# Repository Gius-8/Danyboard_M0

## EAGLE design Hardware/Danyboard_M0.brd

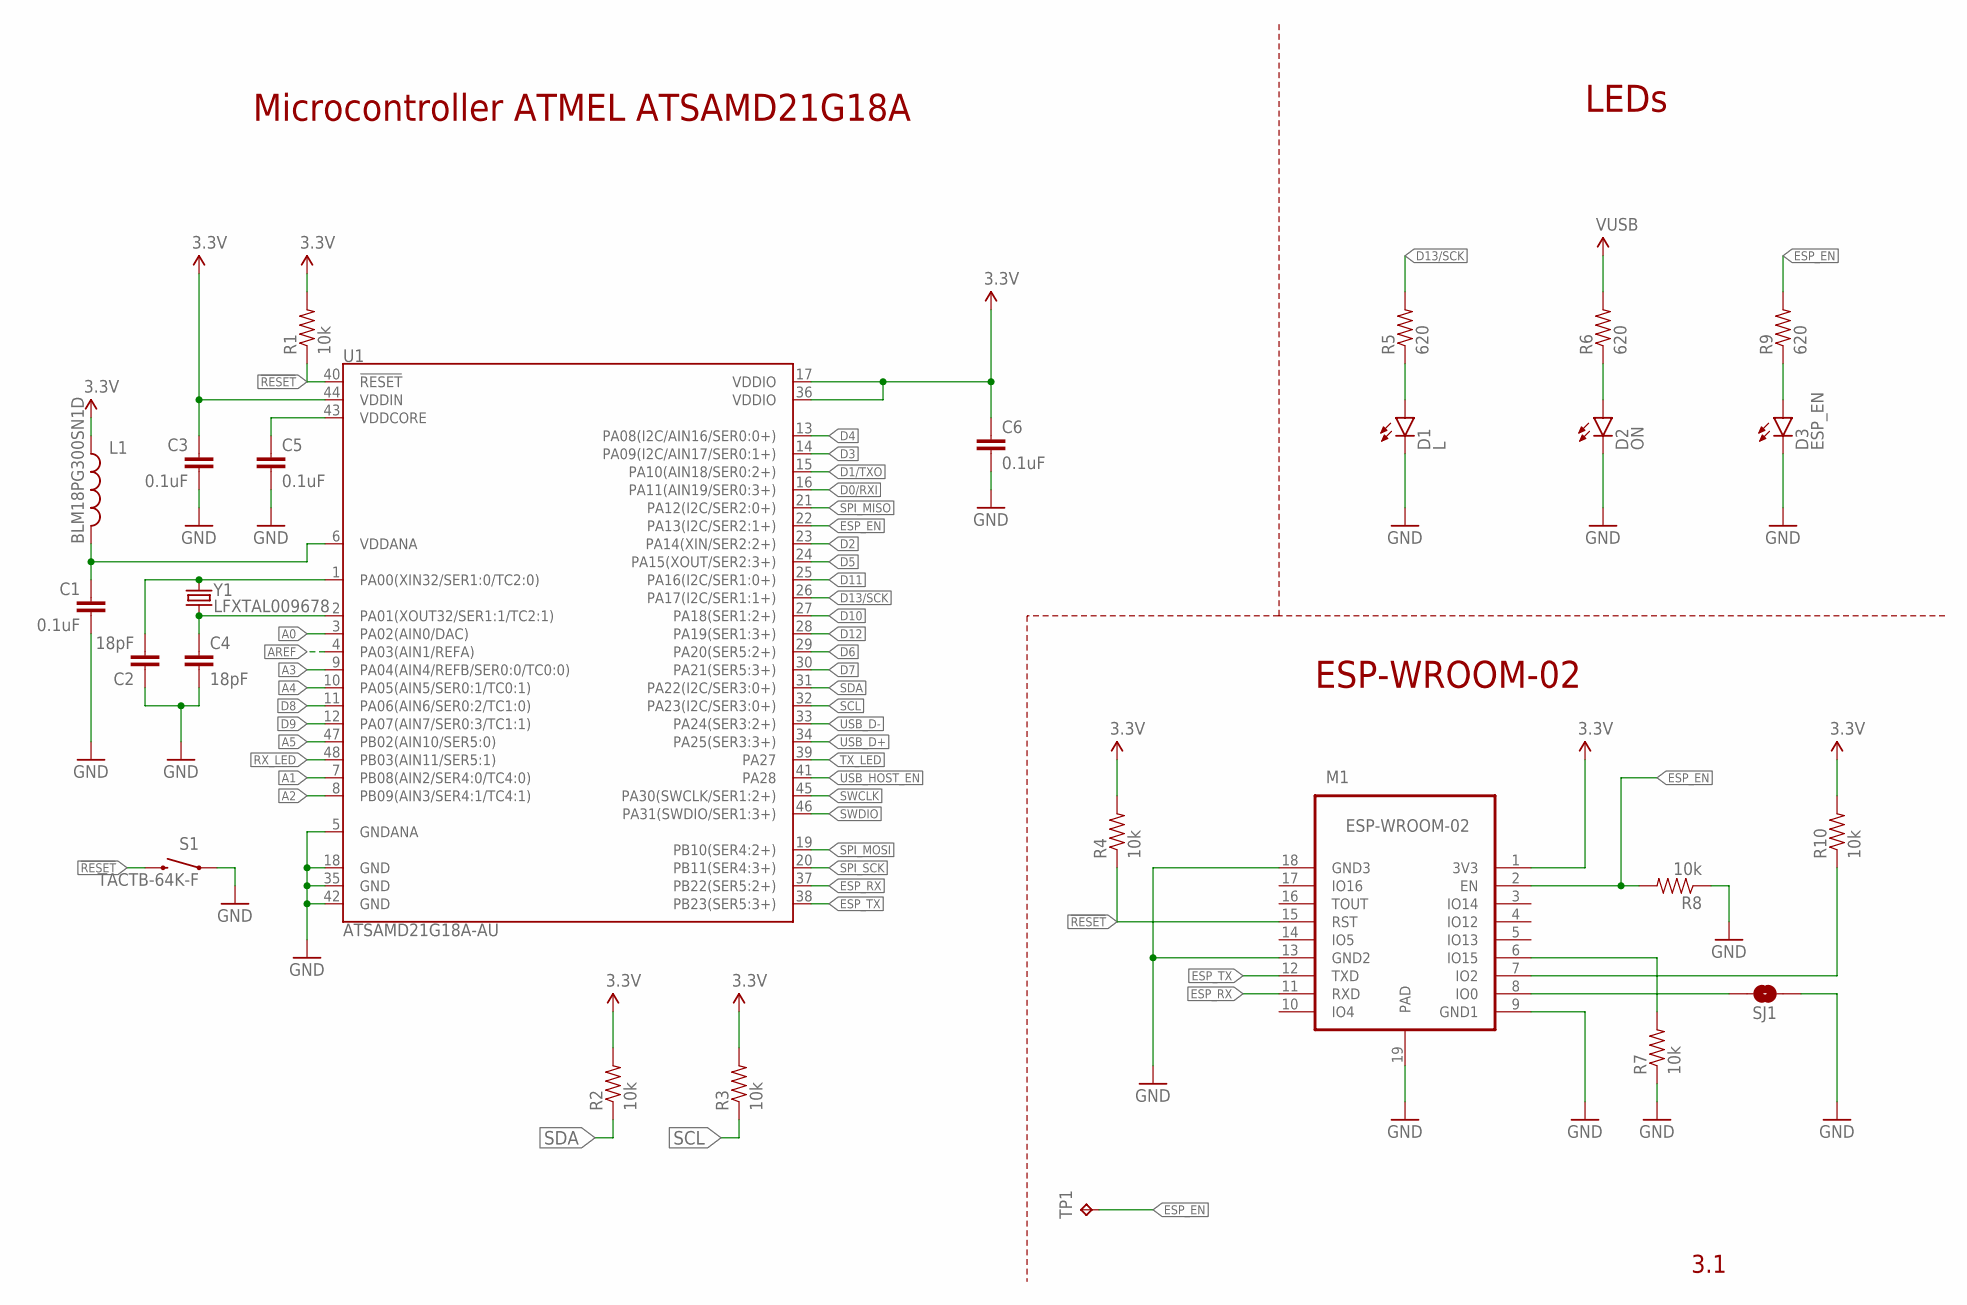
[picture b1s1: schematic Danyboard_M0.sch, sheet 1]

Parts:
C1, C3, C5, C6: 0.1uF; 0603-CAP_NOSILK
C2, C4: 18pF; 0603-CAP_NOSILK
D1: L; LED-0603
D2: ON; LED-0603
D3: ESP_EN; LED-0603
L1: BLM18PG300SN1D; 0603_NOSILK
M1: ESP-WROOM-02; ESP-WROOM-02_NOSILK
R1, R2, R3, R4, R7, R8, R10: 10k; 0603-RES_NOSILK
R5, R6, R9: 620; 0603-RES_NOSILK
S1: TACTB-64K-F; TACTILE-SWITCH-SMD_NOSILK
SJ1: SOLDERJUMPERNO; SJ_2S-NO
TP1: ESP8266; B1,27
U1: ATSAMD21G18A-AU; TQFP-48_NOSILK
Y1: LFXTAL009678; CRYSTAL-SMD-3.2X1.5MM_NOSILK

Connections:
3.3V: C3.1, C6.1, L1.1, M1.1 (3V3), R1.2, R2.2, R3.2, R4.2, R10.2, U1.17 (VDDIO), U1.36 (VDDIO), U1.44 (VDDIN); also elsewhere on the board
!RESET: M1.15 (RST), R1.1, R4.1, S1.3 (2), U1.40 (!RESET!); also elsewhere on the board
A0: U1.3 (PA02(AIN0/DAC)); also elsewhere on the board
A1: U1.7 (PB08(AIN2/SER4:0/TC4:0)); also elsewhere on the board
A2: U1.8 (PB09(AIN3/SER4:1/TC4:1)); also elsewhere on the board
A3: U1.9 (PA04(AIN4/REFB/SER0:0/TC0:0)); also elsewhere on the board
A4: U1.10 (PA05(AIN5/SER0:1/TC0:1)); also elsewhere on the board
A5: U1.47 (PB02(AIN10/SER5:0)); also elsewhere on the board
AREF: U1.4 (PA03(AIN1/REFA)); also elsewhere on the board
D0/RXI: U1.16 (PA11(AIN19/SER0:3+)); also elsewhere on the board
D1/TXO: U1.15 (PA10(AIN18/SER0:2+)); also elsewhere on the board
D2: U1.23 (PA14(XIN/SER2:2+)); also elsewhere on the board
D3: U1.14 (PA09(I2C/AIN17/SER0:1+)); also elsewhere on the board
D4: U1.13 (PA08(I2C/AIN16/SER0:0+)); also elsewhere on the board
D5: U1.24 (PA15(XOUT/SER2:3+)); also elsewhere on the board
D6: U1.29 (PA20(SER5:2+)); also elsewhere on the board
D7: U1.30 (PA21(SER5:3+)); also elsewhere on the board
D8: U1.11 (PA06(AIN6/SER0:2/TC1:0)); also elsewhere on the board
D9: U1.12 (PA07(AIN7/SER0:3/TC1:1)); also elsewhere on the board
D10: U1.27 (PA18(SER1:2+)); also elsewhere on the board
D11: U1.25 (PA16(I2C/SER1:0+)); also elsewhere on the board
D12: U1.28 (PA19(SER1:3+)); also elsewhere on the board
D13/SCK: R5.2, U1.26 (PA17(I2C/SER1:1+)); also elsewhere on the board
ESP_EN: M1.2 (EN), R8.2, R9.2, TP1.TP, U1.22 (PA13(I2C/SER2:1+))
ESP_RX: M1.11 (RXD), U1.37 (PB22(SER5:2+))
ESP_TX: M1.12 (TXD), U1.38 (PB23(SER5:3+))
GND: C1.2, C2.1, C3.2, C4.2, C5.2, C6.2, D1.C, D2.C, D3.C, M1.9 (GND1), M1.13 (GND2), M1.18 (GND3), M1.19 (PAD), R7.1, R8.1, S1.1, SJ1.2, U1.5 (GNDANA), U1.18 (GND), U1.35 (GND), U1.42 (GND); also elsewhere on the board
unnamed: C2.2, U1.1 (PA00(XIN32/SER1:0/TC2:0)), Y1.P$2 (2)
unnamed: C4.1, U1.2 (PA01(XOUT32/SER1:1/TC2:1)), Y1.P$1 (1)
unnamed: D1.A, R5.1
unnamed: M1.6 (IO15), R7.2
unnamed: M1.7 (IO2), R10.1
unnamed: M1.8 (IO0), SJ1.1
unnamed: D3.A, R9.1
unnamed: D2.A, R6.1
RX_LED: U1.48 (PB03(AIN11/SER5:1))
SCL: R3.1, U1.32 (PA23(I2C/SER3:0+)); also elsewhere on the board
SDA: R2.1, U1.31 (PA22(I2C/SER3:0+)); also elsewhere on the board
SPI_MISO: U1.21 (PA12(I2C/SER2:0+)); also elsewhere on the board
SPI_MOSI: U1.19 (PB10(SER4:2+)); also elsewhere on the board
SPI_SCK: U1.20 (PB11(SER4:3+)); also elsewhere on the board
SWCLK: U1.45 (PA30(SWCLK/SER1:2+)); also elsewhere on the board
SWDIO: U1.46 (PA31(SWDIO/SER1:3+)); also elsewhere on the board
TX_LED: U1.39 (PA27)
USB_D+: U1.34 (PA25(SER3:3+)); also elsewhere on the board
USB_D-: U1.33 (PA24(SER3:2+)); also elsewhere on the board
USB_HOST_EN: U1.41 (PA28)
VDDANA: C1.1, L1.2, U1.6 (VDDANA)
VDDCORE: C5.1, U1.43 (VDDCORE)
VUSB: R6.2; also elsewhere on the board

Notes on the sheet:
Microcontroller ATMEL ATSAMD21G18A
LEDs
ESP-WROOM-02
3.1

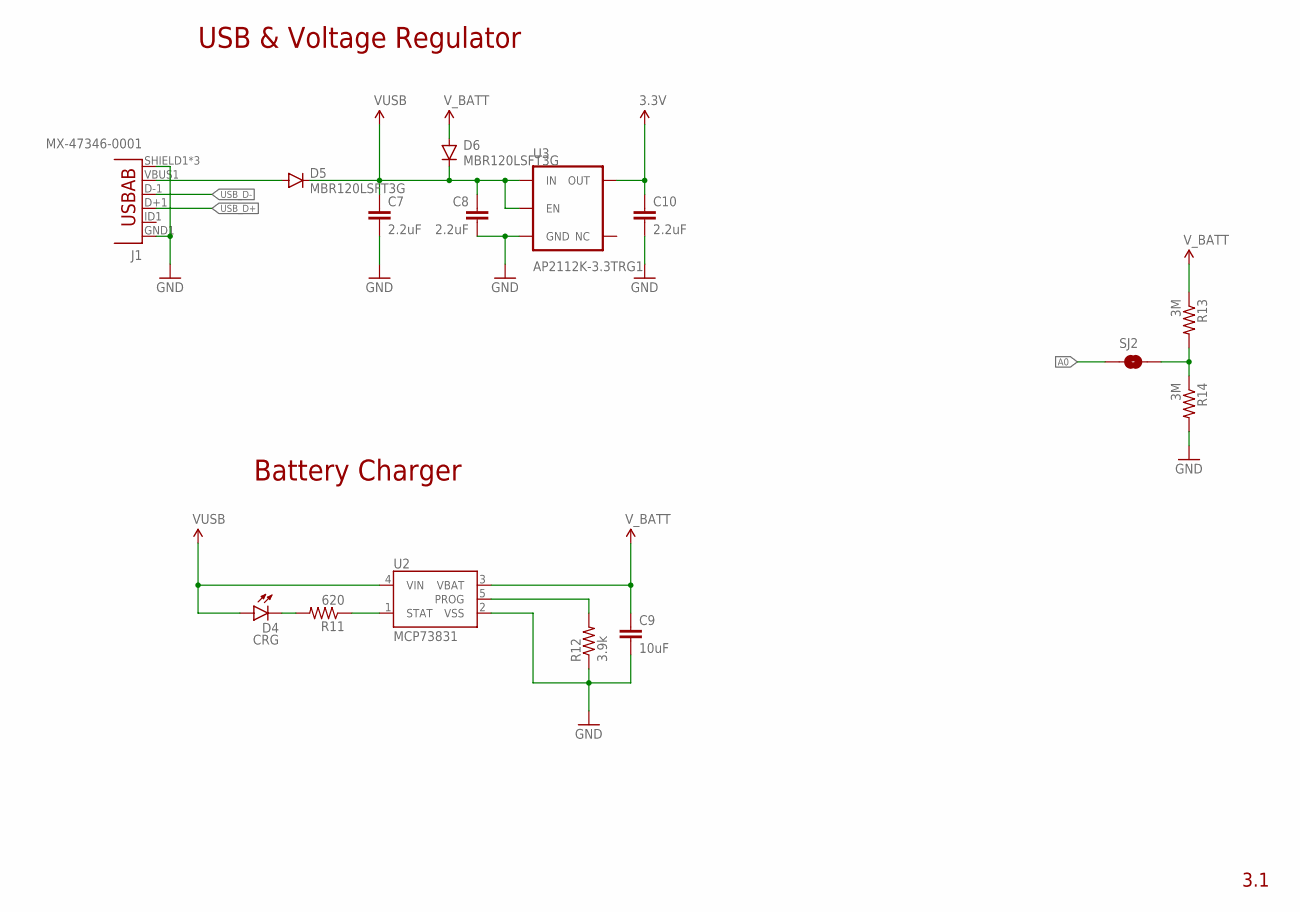
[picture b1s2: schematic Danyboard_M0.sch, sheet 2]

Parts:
C7, C8, C10: 2.2uF; 0603-CAP_NOSILK
C9: 10uF; 0603-CAP_NOSILK
D4: CRG; LED-0603
D5, D6: MBR120LSFT3G; SOD-123_NOSILK
J1: MX-47346-0001; USB-AB-MICRO-SMD_V03
R11: 620; 0603-RES_NOSILK
R12: 3.9k; 0603-RES_NOSILK
R13, R14: 3M; 0603-RES_NOSILK
SJ2: SOLDERJUMPERNO; SJ_2S-NO
U2: MCP73831; SOT23-5
U3: AP2112K-3.3TRG1; SOT23-5

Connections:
3.3V: C10.1, U3.5 (OUT); also elsewhere on the board
A0: SJ2.1; also elsewhere on the board
GND: C7.2, C8.2, C9.2, C10.2, J1.GND1 (GND), J1.SHIELD1 (SHIELD), J1.SHIELD2 (SHIELD), J1.SHIELD3 (SHIELD), R12.1, R14.2, U2.2 (VSS), U3.2 (GND); also elsewhere on the board
unnamed: D4.C, R11.2
unnamed: R11.1, U2.1 (STAT)
unnamed: R12.2, U2.5 (PROG)
unnamed: R13.2, R14.1, SJ2.2
unnamed: D5.A, J1.VBUS1 (VBUS)
USB_D+: J1.D+1 (D+); also elsewhere on the board
USB_D-: J1.D-1 (D-); also elsewhere on the board
VUSB: C7.1, C8.1, D4.A, D5.C, D6.C, U2.4 (VIN), U3.1 (IN), U3.3 (EN); also elsewhere on the board
V_BATT: C9.1, D6.A, R13.1, U2.3 (VBAT); also elsewhere on the board

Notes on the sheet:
USB & Voltage Regulator
Battery Charger
3.1

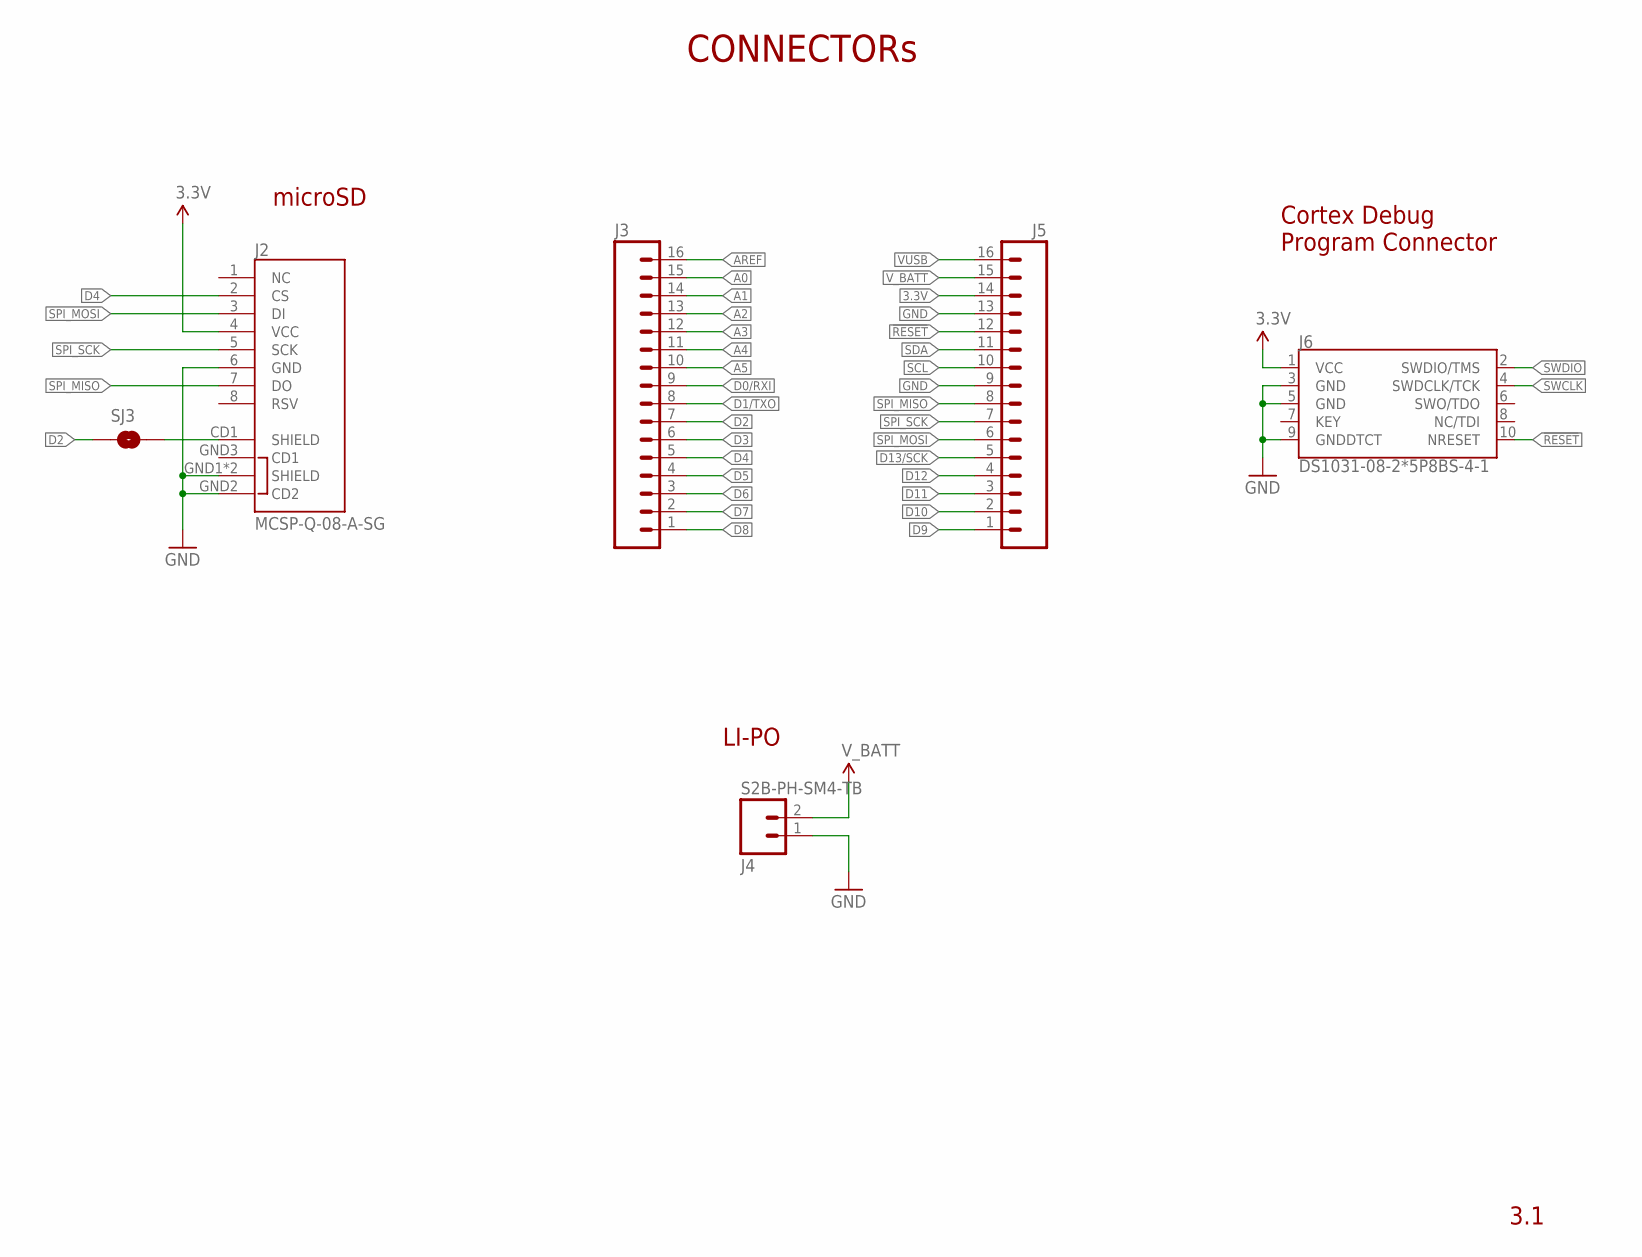
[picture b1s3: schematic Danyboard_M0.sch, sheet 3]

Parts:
J2: MCSP-Q-08-A-SG; MCSP-Q-08-A-SG-T_NOSILK
J3, J5: M161X16_NO_SILK; 1X16_NO_SILK
J4: S2B-PH-SM4-TB; JST-2-SMD_NOSILK
J6: DS1031-08-2*5P8BS-4-1; SAMTECH_FTSH-105-01_NOSILK
SJ3: SOLDERJUMPERNO; SJ_2S-NO

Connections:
3.3V: J2.4 (VCC), J5.14, J6.1 (VCC); also elsewhere on the board
!RESET: J5.12, J6.10 (NRESET); also elsewhere on the board
A0: J3.15; also elsewhere on the board
A1: J3.14; also elsewhere on the board
A2: J3.13; also elsewhere on the board
A3: J3.12; also elsewhere on the board
A4: J3.11; also elsewhere on the board
A5: J3.10; also elsewhere on the board
AREF: J3.16; also elsewhere on the board
D0/RXI: J3.9; also elsewhere on the board
D1/TXO: J3.8; also elsewhere on the board
D2: J3.7, SJ3.1; also elsewhere on the board
D3: J3.6; also elsewhere on the board
D4: J2.2 (CS), J3.5; also elsewhere on the board
D5: J3.4; also elsewhere on the board
D6: J3.3; also elsewhere on the board
D7: J3.2; also elsewhere on the board
D8: J3.1; also elsewhere on the board
D9: J5.1; also elsewhere on the board
D10: J5.2; also elsewhere on the board
D11: J5.3; also elsewhere on the board
D12: J5.4; also elsewhere on the board
D13/SCK: J5.5; also elsewhere on the board
GND: J2.6 (GND), J2.GND1 (SHIELD), J2.GND2 (CD2), J2.GND4 (SHIELD), J4.1 (2), J5.9, J5.13, J6.3 (GND), J6.5 (GND), J6.9 (GNDDTCT); also elsewhere on the board
unnamed: J2.CD1 (SHIELD), SJ3.2
SCL: J5.10; also elsewhere on the board
SDA: J5.11; also elsewhere on the board
SPI_MISO: J2.7 (DO), J5.8; also elsewhere on the board
SPI_MOSI: J2.3 (DI), J5.6; also elsewhere on the board
SPI_SCK: J2.5 (SCK), J5.7; also elsewhere on the board
SWCLK: J6.4 (SWDCLK/TCK); also elsewhere on the board
SWDIO: J6.2 (SWDIO/TMS); also elsewhere on the board
VUSB: J5.16; also elsewhere on the board
V_BATT: J4.2 (1), J5.15; also elsewhere on the board

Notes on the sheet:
Cortex Debug Program Connector
CONNECTORs
microSD
LI-PO
3.1

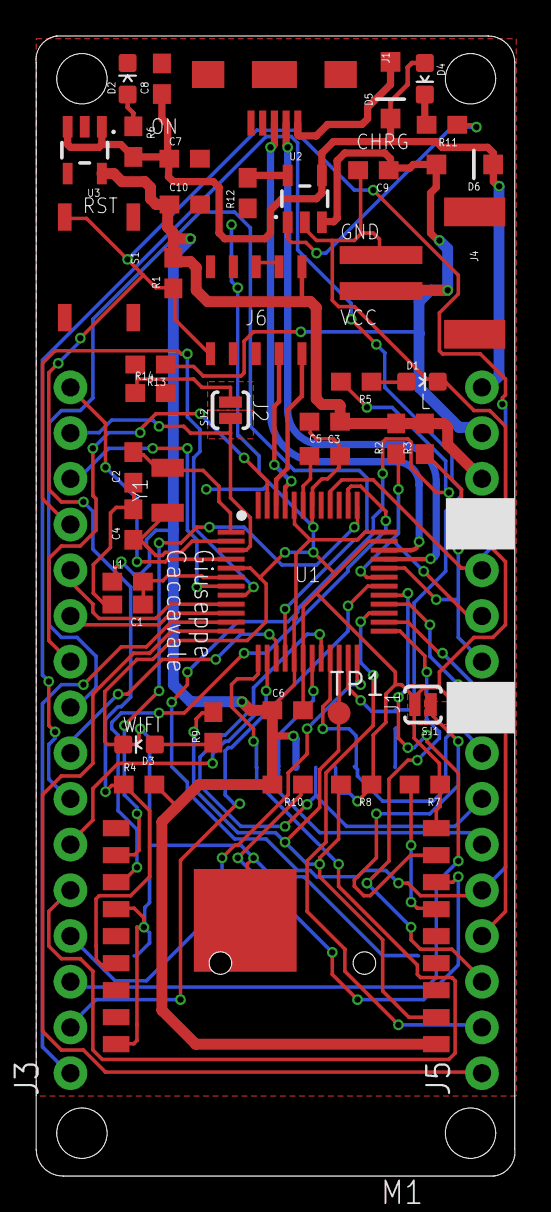
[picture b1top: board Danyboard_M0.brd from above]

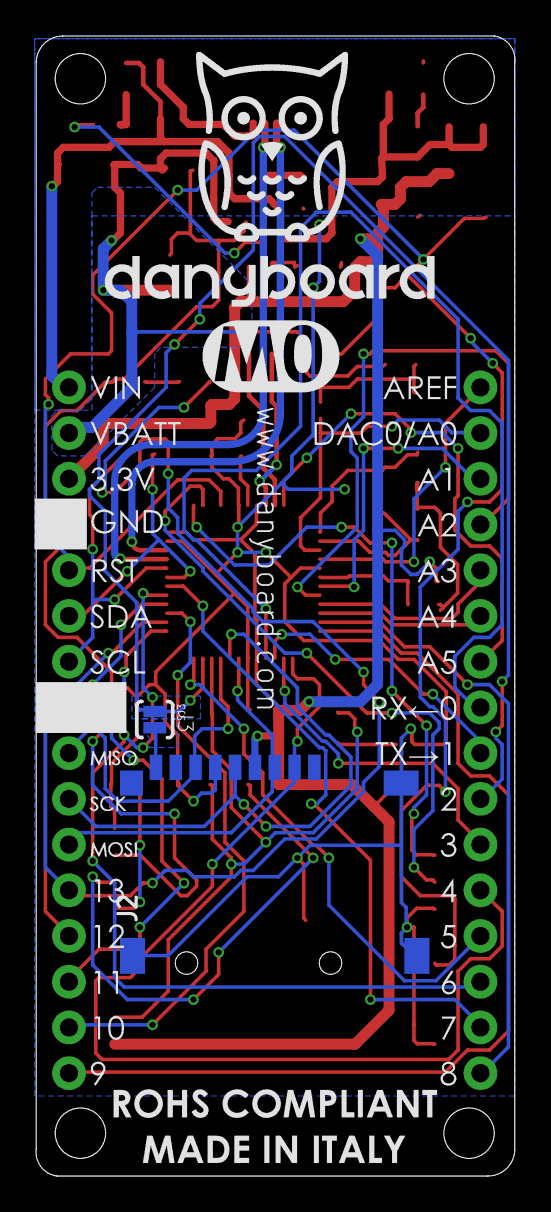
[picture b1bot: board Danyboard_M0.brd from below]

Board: 2 copper layers, 26.6 x 63.3 mm, 48 parts (3 on the bottom side), 54 nets.

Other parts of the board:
U$2: DANYBOARD_M0_FONTPRINT_BOTTOM_NEW

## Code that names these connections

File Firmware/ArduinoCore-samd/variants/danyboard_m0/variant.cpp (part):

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 * +------------+------------------+--------+-----------------+--------------------------------------------------------------------------------------------------------
 * |            | Digital Low      |        |                 |
 * +------------+------------------+--------+-----------------+--------------------------------------------------------------------------------------------------------
 * | 0          | 0 -> RX          |  PA11  |                 | EIC/EXTINT[11] ADC/AIN[19]           PTC/X[3] *SERCOM0/PAD[3]  SERCOM2/PAD[3]  TCC0/WO[3]  TCC1/WO[1]
 * | 1          | 1 <- TX          |  PA10  |                 | EIC/EXTINT[10] ADC/AIN[18]           PTC/X[2] *SERCOM0/PAD[2]                  TCC0/WO[2]  TCC1/WO[0]
 * | 2          | 2                |  PA14  |                 | EIC/EXTINT[14]                                 SERCOM2/PAD[2]  SERCOM4/PAD[2]  TC3/WO[0]   TCC0/WO[4]
 * | 3          | ~3               |  PA09  |                 | EIC/EXTINT[9]  ADC/AIN[17]           PTC/X[1]  SERCOM0/PAD[1]  SERCOM2/PAD[1] *TCC0/WO[1]  TCC1/WO[3]
 * | 4          | ~4               |  PA08  |                 | EIC/NMI        ADC/AIN[16]           PTC/X[0]  SERCOM0/PAD[0]  SERCOM2/PAD[0] *TCC0/WO[0]  TCC1/WO[2]
 * | 5          | ~5               |  PA15  |                 | EIC/EXTINT[15]                                 SERCOM2/PAD[3]  SERCOM4/PAD[3] *TC3/WO[1]   TCC0/WO[5]
 * | 6          | ~6               |  PA20  |                 | EIC/EXTINT[4]                        PTC/X[8]  SERCOM5/PAD[2]  SERCOM3/PAD[2]             *TCC0/WO[6]
 * | 7          | 7                |  PA21  |                 | EIC/EXTINT[5]                        PTC/X[9]  SERCOM5/PAD[3]  SERCOM3/PAD[3]              TCC0/WO[7]
 * +------------+------------------+--------+-----------------+--------------------------------------------------------------------------------------------------------
 * |            | Digital High     |        |                 |
 * +------------+------------------+--------+-----------------+--------------------------------------------------------------------------------------------------------
 * | 8          | ~8               |  PA06  |                 | EIC/EXTINT[6]  ADC/AIN[6]  AC/AIN[2] PTC/Y[4]  SERCOM0/PAD[2]                 *TCC1/WO[0]
 * | 9          | ~9               |  PA07  |                 | EIC/EXTINT[7]  ADC/AIN[7]  AC/AIN[3] PTC/Y[5]  SERCOM0/PAD[3]                 *TCC1/WO[1]
 * | 10         | ~10              |  PA18  |                 | EIC/EXTINT[2]                        PTC/X[6] +SERCOM1/PAD[2]  SERCOM3/PAD[2] *TC3/WO[0]    TCC0/WO[2]
 * | 11         | ~11              |  PA16  |                 | EIC/EXTINT[0]                        PTC/X[4] +SERCOM1/PAD[0]  SERCOM3/PAD[0] *TCC2/WO[0]   TCC0/WO[6]
 * | 12         | ~12              |  PA19  |                 | EIC/EXTINT[3]                        PTC/X[7] +SERCOM1/PAD[3]  SERCOM3/PAD[3]  TC3/WO[1]   *TCC0/WO[3]
 * | 13         | ~13              |  PA17  | LED             | EIC/EXTINT[1]                        PTC/X[5] +SERCOM1/PAD[1]  SERCOM3/PAD[1] *TCC2/WO[1]   TCC0/WO[7]
 * +------------+------------------+--------+-----------------+--------------------------------------------------------------------------------------------------------
 * |            | Analog Connector |        |                 |
 * +------------+------------------+--------+-----------------+--------------------------------------------------------------------------------------------------------
 * | 14         | A0               |  PA02  | A0              | EIC/EXTINT[2] *ADC/AIN[0]  DAC/VOUT  PTC/Y[0]
 * | 15         | A1               |  PB08  | A1              | EIC/EXTINT[8] *ADC/AIN[2]            PTC/Y[14] SERCOM4/PAD[0]                  TC4/WO[0]
 * | 16         | A2               |  PB09  | A2              | EIC/EXTINT[9] *ADC/AIN[3]            PTC/Y[15] SERCOM4/PAD[1]                  TC4/WO[1]
 * | 17         | A3               |  PA04  | A3              | EIC/EXTINT[4] *ADC/AIN[4]  AC/AIN[0] PTC/Y[2]  SERCOM0/PAD[0]                  TCC0/WO[0]
 * | 18         | A4               |  PA05  | A4              | EIC/EXTINT[5] *ADC/AIN[5]  AC/AIN[1] PTC/Y[5]  SERCOM0/PAD[1]                  TCC0/WO[1]
 * | 19         | A5               |  PB02  | A5              | EIC/EXTINT[2] *ADC/AIN[10]           PTC/Y[8]  SERCOM5/PAD[0]
 * +------------+------------------+--------+-----------------+--------------------------------------------------------------------------------------------------------
 * |            | Wire             |        |                 |
 * +------------+------------------+--------+-----------------+--------------------------------------------------------------------------------------------------------
 * | 20         | SDA              |  PA22  | SDA             | EIC/EXTINT[6]                        PTC/X[10] *SERCOM3/PAD[0] SERCOM5/PAD[0] TC4/WO[0] TCC0/WO[4]
 * | 21         | SCL              |  PA23  | SCL             | EIC/EXTINT[7]                        PTC/X[11] *SERCOM3/PAD[1] SERCOM5/PAD[1] TC4/WO[1] TCC0/WO[5]
 * +------------+------------------+--------+-----------------+--------------------------------------------------------------------------------------------------------
 * |            |SPI (Legacy ICSP) |        |                 |
 * +------------+------------------+--------+-----------------+--------------------------------------------------------------------------------------------------------
 * | 22         | 1                |  PA12  | MISO            | EIC/EXTINT[12] SERCOM2/PAD[0] *SERCOM4/PAD[0] TCC2/WO[0] TCC0/WO[6]
 * |            | 2                |        | 5V0             |
 * | 23         | 4                |  PB10  | MOSI            | EIC/EXTINT[10]                *SERCOM4/PAD[2] TC5/WO[0]  TCC0/WO[4]
 * | 24         | 3                |  PB11  | SCK             | EIC/EXTINT[11]                *SERCOM4/PAD[3] TC5/WO[1]  TCC0/WO[5]
 * |            | 5                |        | RESET           |
 * |            | 6                |        | GND             |
 * +------------+------------------+--------+-----------------+--------------------------------------------------------------------------------------------------------
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 * |            | USB              |        |                 |
 * +------------+------------------+--------+-----------------+--------------------------------------------------------------------------------------------------------
 * | 27         |                  |  PA28  | USB_HOST_ENABLE | EIC/EXTINT[8]
 * | 28         |                  |  PA24  | USB_NEGATIVE    | *USB/DM
 * | 29         |                  |  PA25  | USB_POSITIVE    | *USB/DP
 * +------------+------------------+--------+-----------------+--------------------------------------------------------------------------------------------------------
 * |            | EDBG             |        |                 |
 * +------------+------------------+--------+-----------------+--------------------------------------------------------------------------------------------------------
 * | 30         |                  |  PB22  | EDBG_UART TX    | *SERCOM5/PAD[2]
 * | 31         |                  |  PB23  | EDBG_UART RX    | *SERCOM5/PAD[3]
 * +------------+------------------+--------+-----------------+--------------------------------------------------------------------------------------------------------
 * | 32         |                  |  PA22  | EDBG_SDA        | Pin 20 (SDA)
 * | 33         |                  |  PA23  | EDBG_SCL        | Pin 21 (SCL)
 * +------------+------------------+--------+-----------------+--------------------------------------------------------------------------------------------------------
 * | 34         |                  |  PA19  | EDBG_MISO       | EIC/EXTINT[3] *SERCOM1/PAD[3] SERCOM3/PAD[3] TC3/WO[1]  TCC0/WO[3]
 * | 35         |                  |  PA16  | EDBG_MOSI       | EIC/EXTINT[0] *SERCOM1/PAD[0] SERCOM3/PAD[0] TCC2/WO[0] TCC0/WO[6]
 * | 36         |                  |  PA18  | EDBG_SS         | EIC/EXTINT[2] *SERCOM1/PAD[2] SERCOM3/PAD[2] TC3/WO[0]  TCC0/WO[2]
 * | 37         |                  |  PA17  | EDBG_SCK        | EIC/EXTINT[1] *SERCOM1/PAD[1] SERCOM3/PAD[1] TCC2/WO[1] TCC0/WO[7]
 * +------------+------------------+--------+-----------------+--------------------------------------------------------------------------------------------------------
 * | 38         | ATN              |  PA13  | EDBG_GPIO0      | EIC/EXTINT[13] SERCOM2/PAD[1] SERCOM4/PAD[1] *TCC2/WO[1] TCC0/WO[7]
 * | 39         |                  |  PA21  | EDBG_GPIO1      | Pin 7
 * | 40         |                  |  PA06  | EDBG_GPIO2      | Pin 8
 * | 41         |                  |  PA07  | EDBG_GPIO3      | Pin 9
 * +------------+------------------+--------+-----------------+--------------------------------------------------------------------------------------------------------
 * |            |                  |        |                 |
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
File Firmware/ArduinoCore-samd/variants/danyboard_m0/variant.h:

/*
  Copyright (c) 2014-2015 Arduino LLC.  All right reserved.

  This library is free software; you can redistribute it and/or
  modify it under the terms of the GNU Lesser General Public
  License as published by the Free Software Foundation; either
  version 2.1 of the License, or (at your option) any later version.

  This library is distributed in the hope that it will be useful,
  but WITHOUT ANY WARRANTY; without even the implied warranty of
  MERCHANTABILITY or FITNESS FOR A PARTICULAR PURPOSE.
  See the GNU Lesser General Public License for more details.

  You should have received a copy of the GNU Lesser General Public
  License along with this library; if not, write to the Free Software
  Foundation, Inc., 51 Franklin St, Fifth Floor, Boston, MA  02110-1301  USA
*/

#ifndef _VARIANT_ARDUINO_ZERO_
#define _VARIANT_ARDUINO_ZERO_

// The definitions here needs a SAMD core >=1.6.10
#define ARDUINO_SAMD_VARIANT_COMPLIANCE 10610

/*----------------------------------------------------------------------------
 *        Definitions
 *----------------------------------------------------------------------------*/

/** Frequency of the board main oscillator */
#define VARIANT_MAINOSC		(32768ul)

/** Master clock frequency */
#define VARIANT_MCK			  (48000000ul)

/*----------------------------------------------------------------------------
 *        Headers
 *----------------------------------------------------------------------------*/

#include "WVariant.h"

#ifdef __cplusplus
#include "SERCOM.h"
#include "Uart.h"
#endif // __cplusplus

#ifdef __cplusplus
extern "C"
{
#endif // __cplusplus

/*----------------------------------------------------------------------------
 *        Pins
 *----------------------------------------------------------------------------*/

// Number of pins defined in PinDescription array
#define PINS_COUNT           (26u)
#define NUM_DIGITAL_PINS     (20u)
#define NUM_ANALOG_INPUTS    (6u)
#define NUM_ANALOG_OUTPUTS   (1u)
#define analogInputToDigitalPin(p)  ((p < 6u) ? (p) + 14u : -1)

#define digitalPinToPort(P)        ( &(PORT->Group[g_APinDescription[P].ulPort]) )
#define digitalPinToBitMask(P)     ( 1 << g_APinDescription[P].ulPin )
//#define analogInPinToBit(P)        ( )
#define portOutputRegister(port)   ( &(port->OUT.reg) )
#define portInputRegister(port)    ( &(port->IN.reg) )
#define portModeRegister(port)     ( &(port->DIR.reg) )
#define digitalPinHasPWM(P)        ( g_APinDescription[P].ulPWMChannel != NOT_ON_PWM || g_APinDescription[P].ulTCChannel != NOT_ON_TIMER )

/*
 * digitalPinToTimer(..) is AVR-specific and is not defined for SAMD
 * architecture. If you need to check if a pin supports PWM you must
 * use digitalPinHasPWM(..).
 *
 * https://github.com/arduino/Arduino/issues/1833
 */
// #define digitalPinToTimer(P)

// LEDs
#define PIN_LED_13           (13u)
#define PIN_LED_RXL          (25u)
#define PIN_LED_TXL          (26u)
#define PIN_LED              PIN_LED_13
#define PIN_LED2             PIN_LED_RXL
#define PIN_LED3             PIN_LED_TXL
#define LED_BUILTIN          PIN_LED_13

/*
 * Analog pins
 */
#define PIN_A0               (14ul)
#define PIN_A1               (15ul)
#define PIN_A2               (16ul)
#define PIN_A3               (17ul)
#define PIN_A4               (18ul)
#define PIN_A5               (19ul)
#define PIN_DAC0             (14ul)

static const uint8_t A0  = PIN_A0;
static const uint8_t A1  = PIN_A1;
static const uint8_t A2  = PIN_A2;
static const uint8_t A3  = PIN_A3;
static const uint8_t A4  = PIN_A4;
static const uint8_t A5  = PIN_A5;
static const uint8_t DAC0 = PIN_DAC0;
#define ADC_RESOLUTION		12

// Other pins
#define PIN_ATN              (38ul)
static const uint8_t ATN = PIN_ATN;

/*
 * Serial interfaces
 */
// Serial (EDBG)
#define PIN_SERIAL_RX       (31ul)
#define PIN_SERIAL_TX       (30ul)
#define PAD_SERIAL_TX       (UART_TX_PAD_2)
#define PAD_SERIAL_RX       (SERCOM_RX_PAD_3)

// Serial1
#define PIN_SERIAL1_RX       (0ul)
#define PIN_SERIAL1_TX       (1ul)
#define PAD_SERIAL1_TX       (UART_TX_PAD_2)
#define PAD_SERIAL1_RX       (SERCOM_RX_PAD_3)

// Serial5 - ESP8266
#define PIN_SERIAL5_RX       (31ul)
#define PIN_SERIAL5_TX       (30ul)
#define PAD_SERIAL5_TX       (UART_TX_PAD_2)
#define PAD_SERIAL5_RX       (SERCOM_RX_PAD_3)

/*
 * SPI Interfaces
 */
#define SPI_INTERFACES_COUNT 1

#define PIN_SPI_MISO         (22u)
#define PIN_SPI_MOSI         (23u)
#define PIN_SPI_SCK          (24u)
#define PERIPH_SPI           sercom4
#define PAD_SPI_TX           SPI_PAD_2_SCK_3
#define PAD_SPI_RX           SERCOM_RX_PAD_0

static const uint8_t SS	  = PIN_A2 ;	// SERCOM4 last PAD is present on A2 but HW SS isn't used. Set here only for reference.
static const uint8_t MOSI = PIN_SPI_MOSI ;
static const uint8_t MISO = PIN_SPI_MISO ;
static const uint8_t SCK  = PIN_SPI_SCK ;

/*
 * Wire Interfaces
 */
#define WIRE_INTERFACES_COUNT 1

#define PIN_WIRE_SDA         (20u)
#define PIN_WIRE_SCL         (21u)
#define PERIPH_WIRE          sercom3
#define WIRE_IT_HANDLER      SERCOM3_Handler

static const uint8_t SDA = PIN_WIRE_SDA;
static const uint8_t SCL = PIN_WIRE_SCL;

/*
 * USB
 */
#define PIN_USB_HOST_ENABLE (27ul)
#define PIN_USB_DM          (28ul)
#define PIN_USB_DP          (29ul)

/*
 * I2S Interfaces
 */
#define I2S_INTERFACES_COUNT 1

#define I2S_DEVICE          0
#define I2S_CLOCK_GENERATOR 3
#define PIN_I2S_SD          (9u)
#define PIN_I2S_SCK         (1u)
#define PIN_I2S_FS          (0u)

#ifdef __cplusplus
}
#endif

/*----------------------------------------------------------------------------
 *        Arduino objects - C++ only
 *----------------------------------------------------------------------------*/

#ifdef __cplusplus

/*	=========================
 *	===== SERCOM DEFINITION
 *	=========================
*/
extern SERCOM sercom0;
extern SERCOM sercom1;
extern SERCOM sercom2;
extern SERCOM sercom3;
extern SERCOM sercom4;
extern SERCOM sercom5;

extern Uart wifi;
extern Uart Serial1;

#endif

// These serial port names are intended to allow libraries and architecture-neutral
// sketches to automatically default to the correct port name for a particular type
// of use.  For example, a GPS module would normally connect to SERIAL_PORT_HARDWARE_OPEN,
// the first hardware serial port whose RX/TX pins are not dedicated to another use.
//
// SERIAL_PORT_MONITOR        Port which normally prints to the Arduino Serial Monitor
//
// SERIAL_PORT_USBVIRTUAL     Port which is USB virtual serial
//
// SERIAL_PORT_LINUXBRIDGE    Port which connects to a Linux system via Bridge library
//
// SERIAL_PORT_HARDWARE       Hardware serial port, physical RX & TX pins.
//
// SERIAL_PORT_HARDWARE_OPEN  Hardware serial ports which are open for use.  Their RX & TX
//                            pins are NOT connected to anything by default.
#define SERIAL_PORT_USBVIRTUAL      Serial
//#define SERIAL_PORT_MONITOR         Serial
// Serial has no physical pins broken out, so it's not listed as HARDWARE port
#define SERIAL_PORT_HARDWARE        Serial1
#define SERIAL_PORT_HARDWARE_OPEN   Serial1

// Alias Serial to SerialUSB
#define Serial                      SerialUSB

#endif /* _VARIANT_ARDUINO_ZERO_ */

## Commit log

2016-12-07 Schematics and PCB design V3.1
2016-12-07 Adding Pinout
2016-12-07 Adding ArduinoCore for Danyboard M0
2017-02-06 Updating ArduinoCore
2017-12-11 v3.2

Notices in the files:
parts and their libraries:
SparkFun-Connectors: Licensing: Creative Commons ShareAlike 4.0 International - https://creativecommons.org/licenses/by-sa/4.0
